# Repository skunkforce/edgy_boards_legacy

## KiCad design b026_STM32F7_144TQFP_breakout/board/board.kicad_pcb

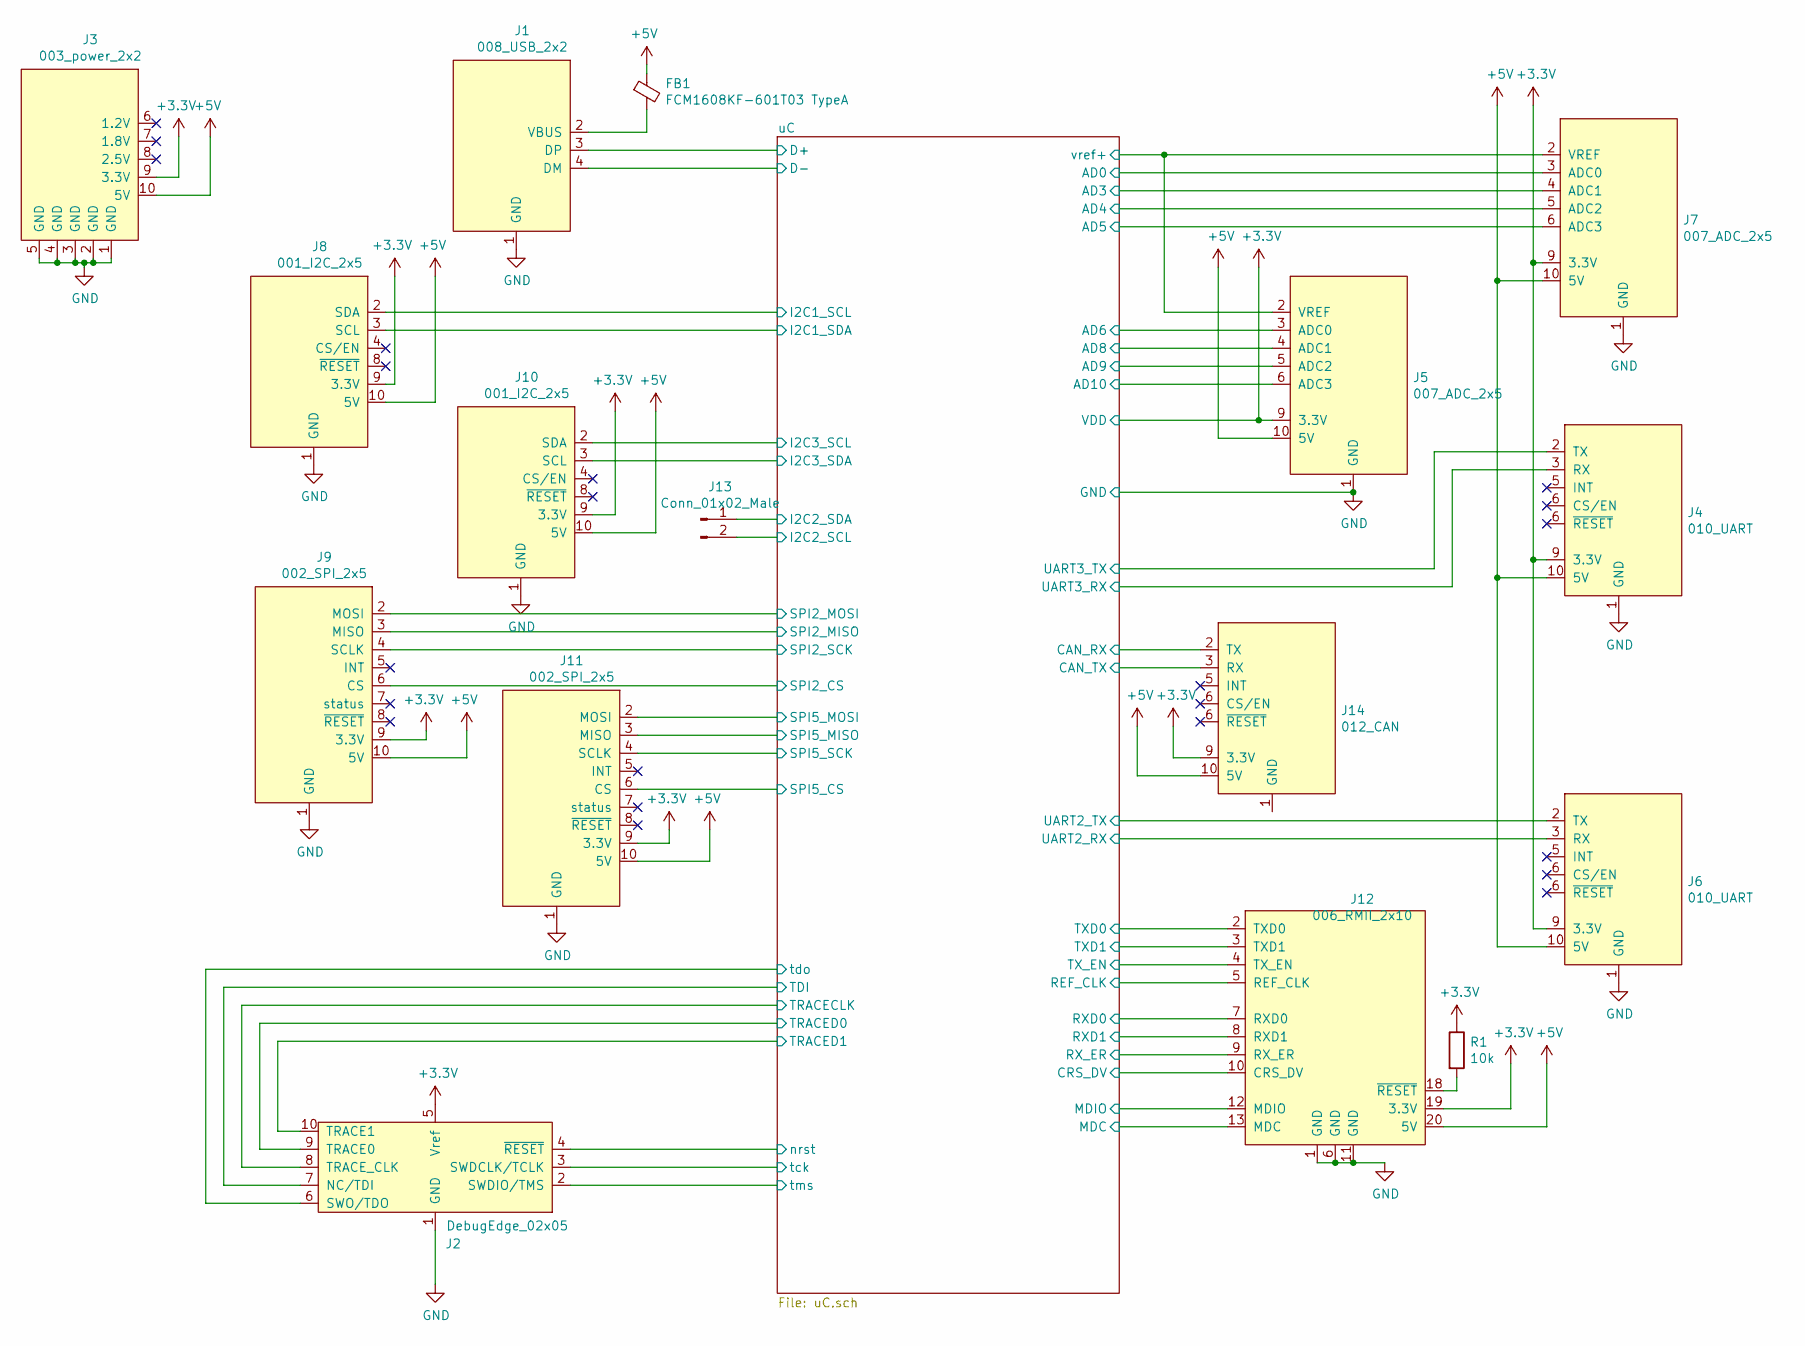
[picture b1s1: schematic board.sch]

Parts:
FB1: FCM1608KF-601T03 TypeA; L_0805_2012Metric
J1: 008_USB_2x2; on_edge_2x05_device
J2: DebugEdge_02x05; on_edge_2x05_device
J3: 003_power_2x2; on_edge_2x05_device
J4: 010_UART; on_edge_2x05_device
J5, J7: 007_ADC_2x5; on_edge_2x05_host
J6: 010_UART; on_edge_2x05_up_host
J8, J10: 001_I2C_2x5; on_edge_2x05_up_host
J9, J11: 002_SPI_2x5; on_edge_2x05_up_host
J12: 006_RMII_2x10; on_edge_2x10_host
J13: Conn_01x02_Male; PinHeader_1x02_P2.00mm_Vertical
J14: 012_CAN; on_edge_2x05_up_host
R1: 10k; R_0603_1608Metric_Pad1.05x0.95mm_HandSolder

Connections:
+3V3: J2.5 (Vref), J3.9 (3.3V), J4.9 (3.3V), J5.9 (3.3V), J6.9 (3.3V), J7.9 (3.3V), J8.9 (3.3V), J9.9 (3.3V), J10.9 (3.3V), J11.9 (3.3V), J12.19 (3.3V), J14.9 (3.3V), R1.1; also elsewhere on the board
+5V: FB1.1, J3.10 (5V), J4.10 (5V), J5.10 (5V), J6.10 (5V), J7.10 (5V), J8.10 (5V), J9.10 (5V), J10.10 (5V), J11.10 (5V), J12.20 (5V), J14.10 (5V)
/uC/AD0: J7.3 (ADC0); also elsewhere on the board
/uC/AD3: J7.4 (ADC1); also elsewhere on the board
/uC/AD4: J7.5 (ADC2); also elsewhere on the board
/uC/AD5: J7.6 (ADC3); also elsewhere on the board
/uC/AD6: J5.3 (ADC0); also elsewhere on the board
/uC/AD8: J5.4 (ADC1); also elsewhere on the board
/uC/AD9: J5.5 (ADC2); also elsewhere on the board
/uC/AD10: J5.6 (ADC3); also elsewhere on the board
/uC/CAN_RX: J14.2 (TX); also elsewhere on the board
/uC/CAN_TX: J14.3 (RX); also elsewhere on the board
/uC/CRS_DV: J12.10 (CRS_DV); also elsewhere on the board
/uC/D+: J1.3 (DP); also elsewhere on the board
/uC/D-: J1.4 (DM); also elsewhere on the board
/uC/I2C1_SCL: J8.2 (SDA); also elsewhere on the board
/uC/I2C1_SDA: J8.3 (SCL); also elsewhere on the board
/uC/I2C2_SCL: J13.2; also elsewhere on the board
/uC/I2C2_SDA: J13.1; also elsewhere on the board
/uC/I2C3_SCL: J10.2 (SDA); also elsewhere on the board
/uC/I2C3_SDA: J10.3 (SCL); also elsewhere on the board
/uC/MDC: J12.13 (MDC); also elsewhere on the board
/uC/MDIO: J12.12 (MDIO); also elsewhere on the board
/uC/REF_CLK: J12.5 (REF_CLK); also elsewhere on the board
/uC/RXD0: J12.7 (RXD0); also elsewhere on the board
/uC/RXD1: J12.8 (RXD1); also elsewhere on the board
/uC/RX_ER: J12.9 (RX_ER); also elsewhere on the board
/uC/SPI2_CS: J9.6 (CS); also elsewhere on the board
/uC/SPI2_MISO: J9.3 (MISO); also elsewhere on the board
/uC/SPI2_MOSI: J9.2 (MOSI); also elsewhere on the board
/uC/SPI2_SCK: J9.4 (SCLK); also elsewhere on the board
/uC/SPI5_CS: J11.6 (CS); also elsewhere on the board
/uC/SPI5_MISO: J11.3 (MISO); also elsewhere on the board
/uC/SPI5_MOSI: J11.2 (MOSI); also elsewhere on the board
/uC/SPI5_SCK: J11.4 (SCLK); also elsewhere on the board
/uC/TDI: J2.7 (NC/TDI); also elsewhere on the board
/uC/TRACECLK: J2.8 (TRACE_CLK); also elsewhere on the board
/uC/TRACED0: J2.9 (TRACE0); also elsewhere on the board
/uC/TRACED1: J2.10 (TRACE1); also elsewhere on the board
/uC/TXD0: J12.2 (TXD0); also elsewhere on the board
/uC/TXD1: J12.3 (TXD1); also elsewhere on the board
/uC/TX_EN: J12.4 (TX_EN); also elsewhere on the board
/uC/UART2_RX: J6.3 (RX); also elsewhere on the board
/uC/UART2_TX: J6.2 (TX); also elsewhere on the board
/uC/UART3_RX: J4.3 (RX); also elsewhere on the board
/uC/UART3_TX: J4.2 (TX); also elsewhere on the board
/uC/nrst: J2.4 (~RESET~); also elsewhere on the board
/uC/tck: J2.3 (SWDCLK/TCLK); also elsewhere on the board
/uC/tdo: J2.6 (SWO/TDO); also elsewhere on the board
/uC/tms: J2.2 (SWDIO/TMS); also elsewhere on the board
/uC/vref+: J5.2 (VREF), J7.2 (VREF); also elsewhere on the board
GND: J1.1 (GND), J2.1 (GND), J3.1 (GND), J3.2 (GND), J3.3 (GND), J3.4 (GND), J3.5 (GND), J4.1 (GND), J5.1 (GND), J6.1 (GND), J7.1 (GND), J8.1 (GND), J9.1 (GND), J10.1 (GND), J11.1 (GND), J12.1 (GND), J12.6 (GND), J12.11 (GND); also elsewhere on the board
unnamed: FB1.2, J1.2 (VBUS)
unnamed: J12.18 (~RESET), R1.2

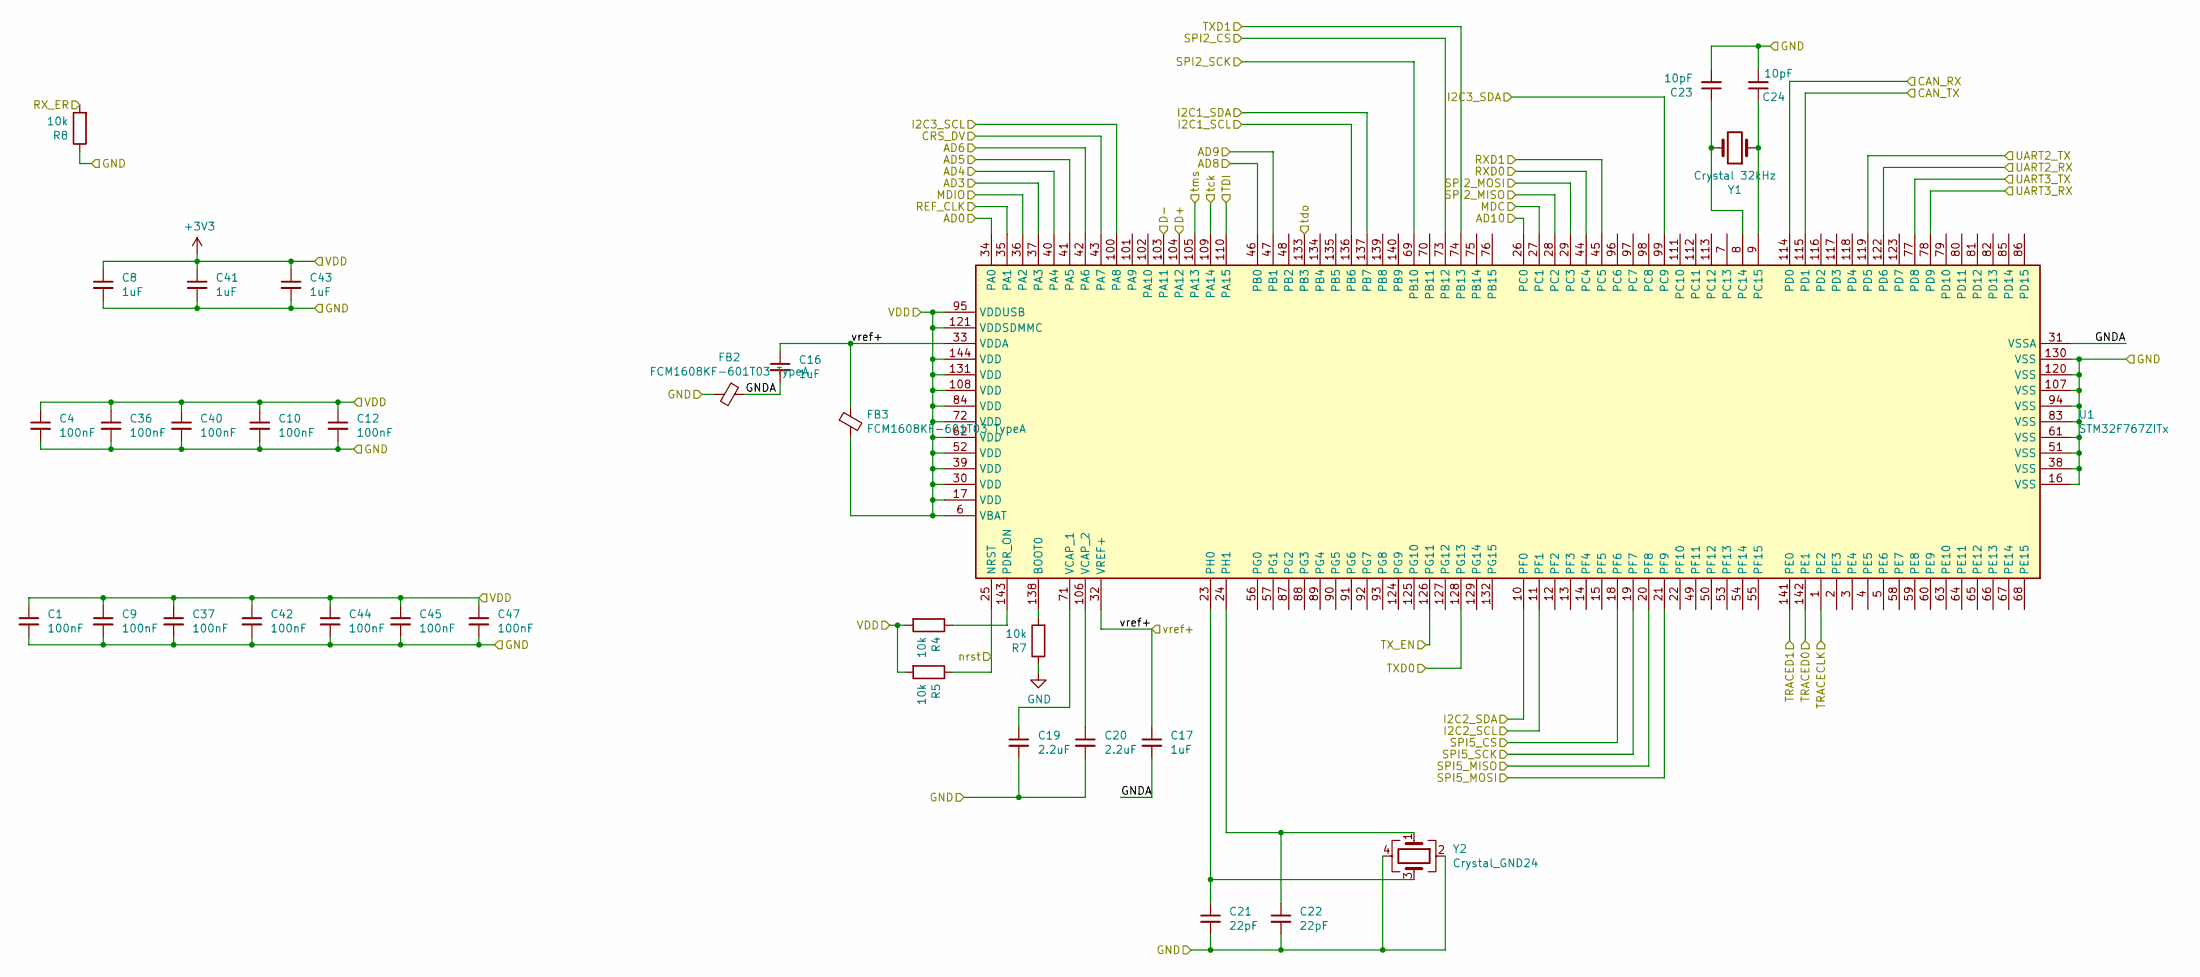
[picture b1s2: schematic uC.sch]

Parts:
C1, C4, C9, C10, C12, C36, C37, C40, C42, C44, C45, C47: 100nF; C_0603_1608Metric
C8, C16, C17, C41, C43: 1uF; C_0603_1608Metric
C19, C20: 2.2uF; C_0603_1608Metric_Pad1.05x0.95mm_HandSolder
C21, C22: 22pF; C_0603_1608Metric_Pad1.05x0.95mm_HandSolder
C23, C24: 10pF; C_0603_1608Metric_Pad1.05x0.95mm_HandSolder
FB2, FB3: FCM1608KF-601T03 TypeA; L_0805_2012Metric
R4, R5, R7, R8: 10k; R_0603_1608Metric_Pad1.05x0.95mm_HandSolder
U1: STM32F767ZITx; LQFP-144_20x20mm_P0.5mm
Y1: Crystal 32kHz; Crystal_SMD_3215-2Pin_3.2x1.5mm; Digi-Key_PN 644-1156-1-ND
Y2: Crystal_GND24; Crystal_SMD_Abracon_ABM8G-4Pin_3.2x2.5mm; Digi-Key_PN 535-9140-1-ND

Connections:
+3V3: C1.1, C4.1, C8.1, C9.1, C10.1, C12.1, C36.1, C37.1, C40.1, C41.1, C42.1, C43.1, C44.1, C45.1, C47.1, FB3.2, R4.2, R5.2, U1.6 (VBAT), U1.17 (VDD), U1.30 (VDD), U1.39 (VDD), U1.52 (VDD), U1.62 (VDD), U1.72 (VDD), U1.84 (VDD), U1.95 (VDDUSB), U1.108 (VDD), U1.121 (VDDSDMMC), U1.131 (VDD), U1.144 (VDD); also elsewhere on the board
/uC/AD0: U1.34 (PA0); also elsewhere on the board
/uC/AD3: U1.37 (PA3); also elsewhere on the board
/uC/AD4: U1.40 (PA4); also elsewhere on the board
/uC/AD5: U1.41 (PA5); also elsewhere on the board
/uC/AD6: U1.42 (PA6); also elsewhere on the board
/uC/AD8: U1.46 (PB0); also elsewhere on the board
/uC/AD9: U1.47 (PB1); also elsewhere on the board
/uC/AD10: U1.26 (PC0); also elsewhere on the board
/uC/CAN_RX: U1.114 (PD0); also elsewhere on the board
/uC/CAN_TX: U1.115 (PD1); also elsewhere on the board
/uC/CRS_DV: U1.43 (PA7); also elsewhere on the board
/uC/D+: U1.104 (PA12); also elsewhere on the board
/uC/D-: U1.103 (PA11); also elsewhere on the board
/uC/GNDA: C16.2, C17.2, FB2.1, U1.31 (VSSA)
/uC/I2C1_SCL: U1.136 (PB6); also elsewhere on the board
/uC/I2C1_SDA: U1.137 (PB7); also elsewhere on the board
/uC/I2C2_SCL: U1.11 (PF1); also elsewhere on the board
/uC/I2C2_SDA: U1.10 (PF0); also elsewhere on the board
/uC/I2C3_SCL: U1.100 (PA8); also elsewhere on the board
/uC/I2C3_SDA: U1.99 (PC9); also elsewhere on the board
/uC/MDC: U1.27 (PC1); also elsewhere on the board
/uC/MDIO: U1.36 (PA2); also elsewhere on the board
/uC/REF_CLK: U1.35 (PA1); also elsewhere on the board
/uC/RXD0: U1.44 (PC4); also elsewhere on the board
/uC/RXD1: U1.45 (PC5); also elsewhere on the board
/uC/RX_ER: R8.2; also elsewhere on the board
/uC/SPI2_CS: U1.73 (PB12); also elsewhere on the board
/uC/SPI2_MISO: U1.28 (PC2); also elsewhere on the board
/uC/SPI2_MOSI: U1.29 (PC3); also elsewhere on the board
/uC/SPI2_SCK: U1.69 (PB10); also elsewhere on the board
/uC/SPI5_CS: U1.18 (PF6); also elsewhere on the board
/uC/SPI5_MISO: U1.20 (PF8); also elsewhere on the board
/uC/SPI5_MOSI: U1.21 (PF9); also elsewhere on the board
/uC/SPI5_SCK: U1.19 (PF7); also elsewhere on the board
/uC/TDI: U1.110 (PA15); also elsewhere on the board
/uC/TRACECLK: U1.1 (PE2); also elsewhere on the board
/uC/TRACED0: U1.142 (PE1); also elsewhere on the board
/uC/TRACED1: U1.141 (PE0); also elsewhere on the board
/uC/TXD0: U1.128 (PG13); also elsewhere on the board
/uC/TXD1: U1.74 (PB13); also elsewhere on the board
/uC/TX_EN: U1.126 (PG11); also elsewhere on the board
/uC/UART2_RX: U1.122 (PD6); also elsewhere on the board
/uC/UART2_TX: U1.119 (PD5); also elsewhere on the board
/uC/UART3_RX: U1.78 (PD9); also elsewhere on the board
/uC/UART3_TX: U1.77 (PD8); also elsewhere on the board
/uC/nrst: R5.1, U1.25 (NRST); also elsewhere on the board
/uC/tck: U1.109 (PA14); also elsewhere on the board
/uC/tdo: U1.133 (PB3); also elsewhere on the board
/uC/tms: U1.105 (PA13); also elsewhere on the board
/uC/vref+: C16.1, C17.1, FB3.1, U1.32 (VREF+), U1.33 (VDDA); also elsewhere on the board
GND: C1.2, C4.2, C8.2, C9.2, C10.2, C12.2, C19.2, C20.2, C21.2, C22.2, C23.2, C24.2, C36.2, C37.2, C40.2, C41.2, C42.2, C43.2, C44.2, C45.2, C47.2, FB2.2, R7.1, R8.1, U1.16 (VSS), U1.38 (VSS), U1.51 (VSS), U1.61 (VSS), U1.83 (VSS), U1.94 (VSS), U1.107 (VSS), U1.120 (VSS), U1.130 (VSS), Y2.2, Y2.4; also elsewhere on the board
unnamed: C19.1, U1.71 (VCAP_1)
unnamed: C20.1, U1.106 (VCAP_2)
unnamed: C21.1, U1.23 (PH0), Y2.3
unnamed: C22.1, U1.24 (PH1), Y2.1
unnamed: C23.1, U1.8 (PC14), Y1.2
unnamed: C24.1, U1.9 (PC15), Y1.1
unnamed: R4.1, U1.143 (PDR_ON)
unnamed: R7.2, U1.138 (BOOT0)

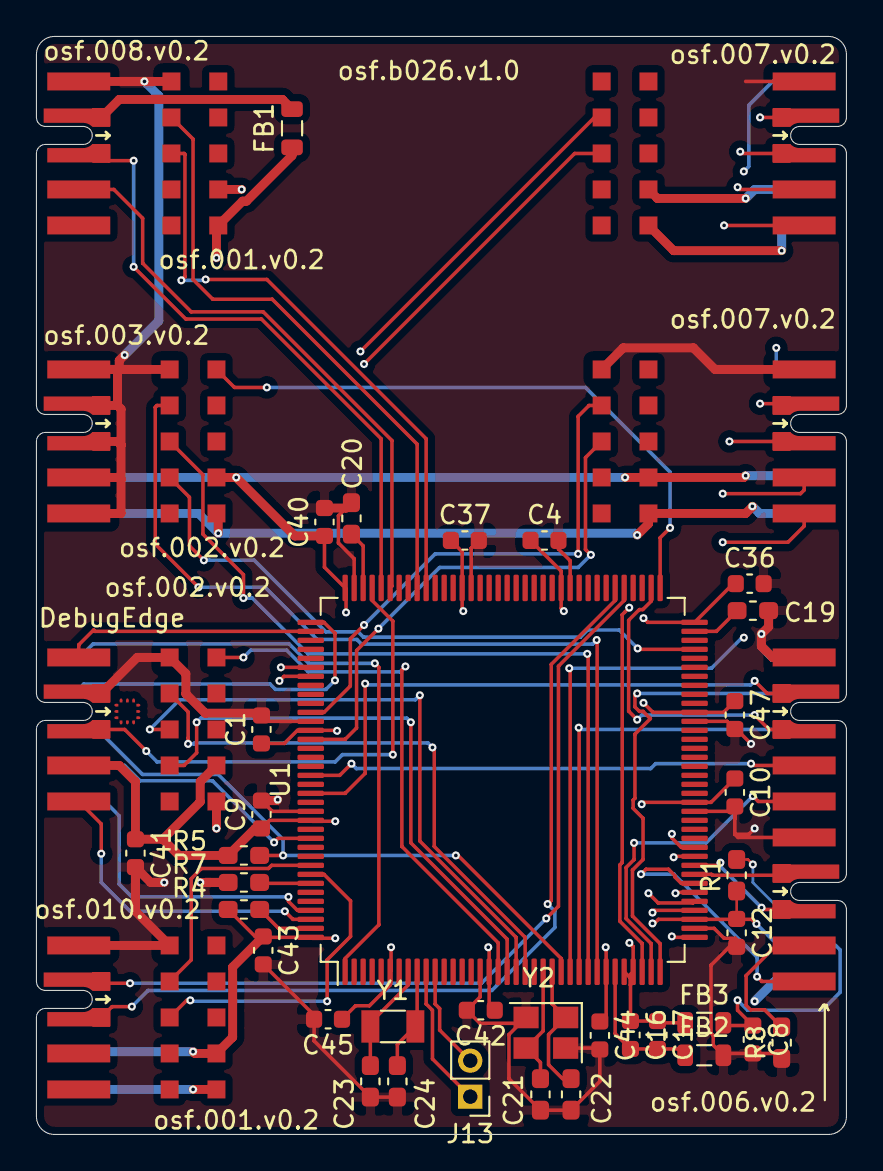
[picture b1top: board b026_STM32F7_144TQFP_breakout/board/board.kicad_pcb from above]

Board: 4 copper layers, 45.0 x 61.0 mm, 48 parts (0 on the bottom side), 63 nets.

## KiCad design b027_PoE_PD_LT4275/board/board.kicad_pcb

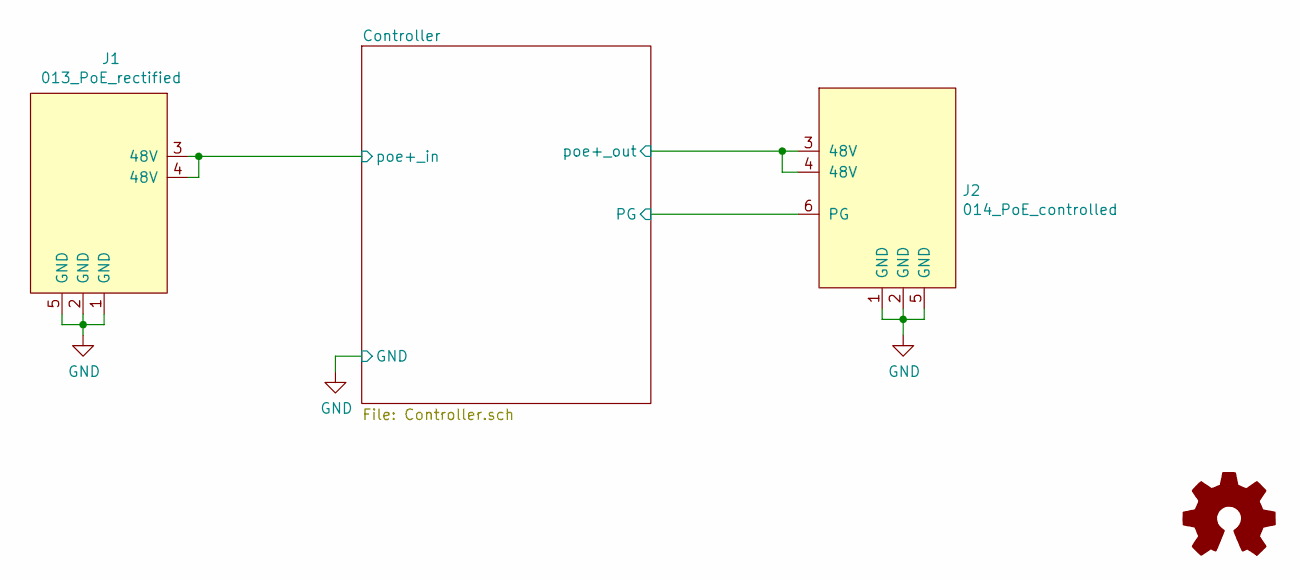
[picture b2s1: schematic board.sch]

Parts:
J1: 013_PoE_rectified; on_edge_2x05_device
J2: 014_PoE_controlled; on_edge_2x05_host
LOGO1: Logo_Open_Hardware_Small; OSHW-Logo2_9.8x8mm_SilkScreen

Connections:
/Controller/PG: J2.6 (PG); also elsewhere on the board
/Controller/poe+_in: J1.3 (48V), J1.4 (48V); also elsewhere on the board
/Controller/poe+_out: J2.3 (48V), J2.4 (48V); also elsewhere on the board
GND: J1.1 (GND), J1.2 (GND), J1.5 (GND), J2.1 (GND), J2.2 (GND), J2.5 (GND); also elsewhere on the board

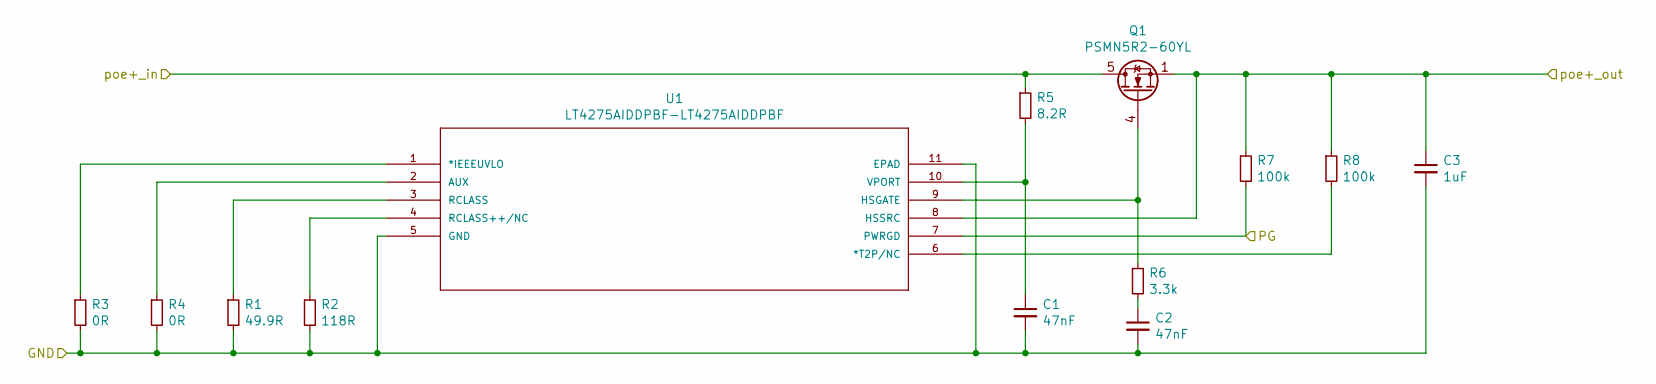
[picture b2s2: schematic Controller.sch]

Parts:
C1, C2: 47nF; C_0603_1608Metric
C3: 1uF; C_1206_3216Metric; Voltage 100
Q1: PSMN5R2-60YL; LFPAK33
R1: 49.9R; R_0603_1608Metric
R2: 118R; R_0603_1608Metric
R3, R4: 0R; R_0603_1608Metric
R5: 8.2R; R_0603_1608Metric
R6: 3.3k; R_0603_1608Metric
R7, R8: 100k; R_0603_1608Metric
U1: LT4275AIDDPBF-LT4275AIDDPBF; DFN-10-1EP_3x3mm_P0.5mm_EP1.65x2.38mm; MANUFACTURER_PART_NUMBER lt4275aidd#pbf

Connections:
/Controller/PG: R7.2, U1.7 (PWRGD); also elsewhere on the board
/Controller/poe+_in: Q1.5 (D), R5.1; also elsewhere on the board
/Controller/poe+_out: C3.1, Q1.1 (S), Q1.2 (S), Q1.3 (S), R7.1, R8.1, U1.8 (HSSRC); also elsewhere on the board
GND: C1.2, C2.2, C3.2, R1.2, R2.2, R3.2, R4.2, U1.5 (GND), U1.11 (EPAD); also elsewhere on the board
unnamed: C1.1, R5.2, U1.10 (VPORT)
unnamed: C2.1, R6.2
unnamed: Q1.4 (G), R6.1, U1.9 (HSGATE)
unnamed: R1.1, U1.3 (RCLASS)
unnamed: R2.1, U1.4 (RCLASS++/NC)
unnamed: R3.1, U1.1 (*IEEEUVLO)
unnamed: R4.1, U1.2 (AUX)
unnamed: R8.2, U1.6 (*T2P/NC)

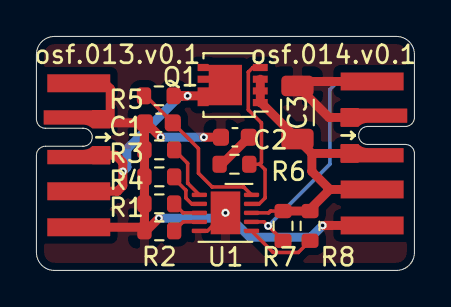
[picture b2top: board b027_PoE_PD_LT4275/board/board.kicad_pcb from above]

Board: 2 copper layers, 21.0 x 13.0 mm, 16 parts (1 on the bottom side), 12 nets.

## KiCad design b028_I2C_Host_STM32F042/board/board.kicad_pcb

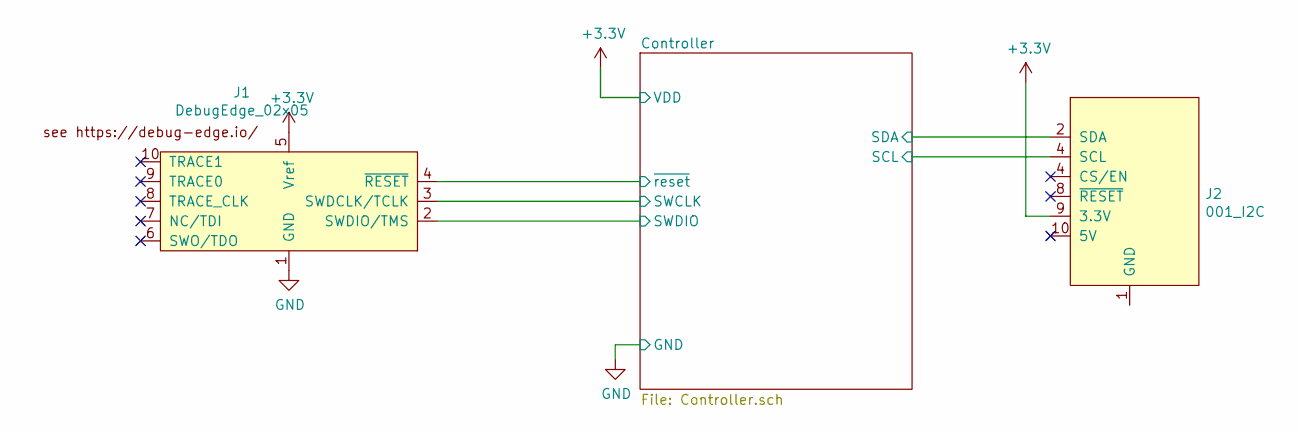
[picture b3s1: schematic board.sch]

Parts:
J1: DebugEdge_02x05; on_edge_2x05_device
J2: 001_I2C; on_edge_2x05_host

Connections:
+3V3: J1.5 (Vref), J2.9 (3.3V); also elsewhere on the board
/Controller/SCL: J2.4 (CS/EN); also elsewhere on the board
/Controller/SDA: J2.2 (SDA); also elsewhere on the board
/Controller/SWCLK: J1.3 (SWDCLK/TCLK); also elsewhere on the board
/Controller/SWDIO: J1.2 (SWDIO/TMS); also elsewhere on the board
/Controller/~reset: J1.4 (~RESET~); also elsewhere on the board
GND: J1.1 (GND); also elsewhere on the board

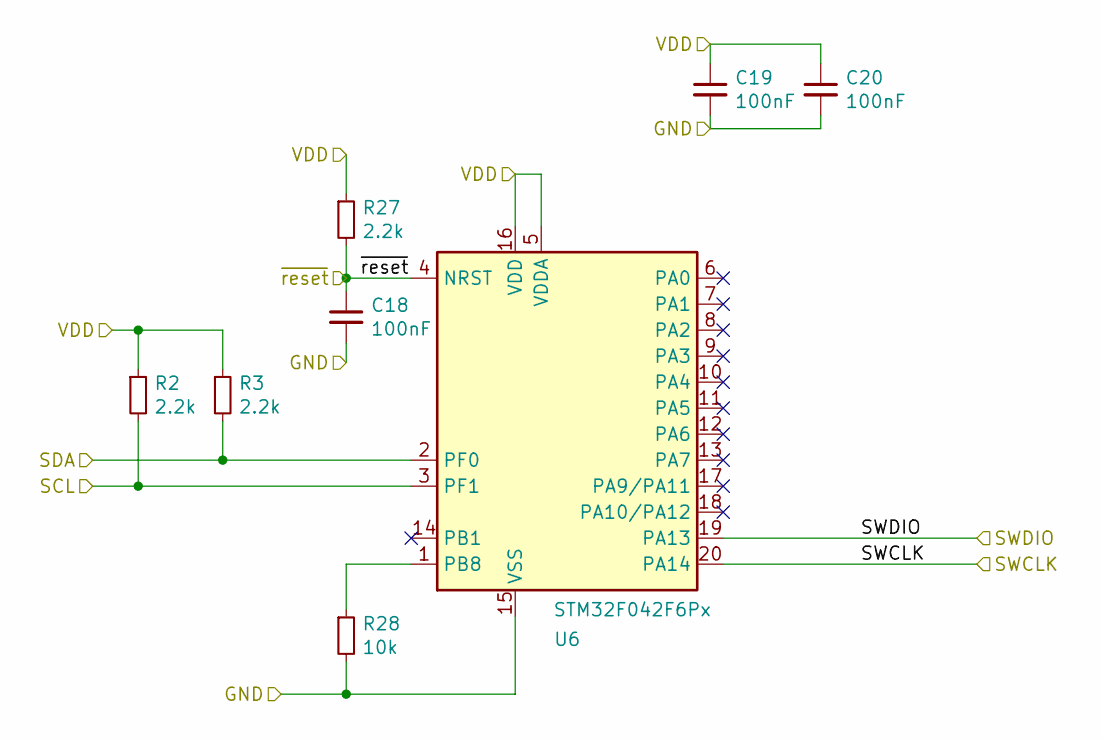
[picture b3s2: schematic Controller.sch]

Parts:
C18, C19, C20: 100nF; C_0603_1608Metric
R2, R3, R27: 2.2k; R_0603_1608Metric
R28: 10k; R_0603_1608Metric
U6: STM32F042F6Px; TSSOP-20_4.4x6.5mm_P0.65mm; MPN STM32F042F4P6; Digi-Key_PN 497-17343-ND

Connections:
+3V3: C19.1, C20.1, R2.1, R3.1, R27.1, U6.5 (VDDA), U6.16 (VDD); also elsewhere on the board
/Controller/SCL: R2.2, U6.3 (PF1); also elsewhere on the board
/Controller/SDA: R3.2, U6.2 (PF0); also elsewhere on the board
/Controller/SWCLK: U6.20 (PA14); also elsewhere on the board
/Controller/SWDIO: U6.19 (PA13); also elsewhere on the board
/Controller/~reset: C18.1, R27.2, U6.4 (NRST); also elsewhere on the board
GND: C18.2, C19.2, C20.2, R28.2, U6.15 (VSS); also elsewhere on the board
unnamed: R28.1, U6.1 (PB8)

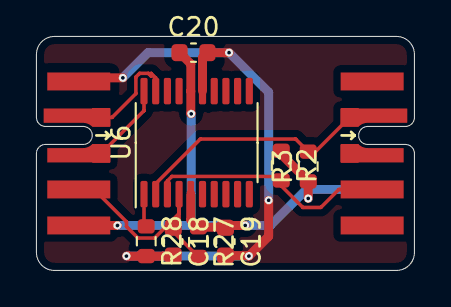
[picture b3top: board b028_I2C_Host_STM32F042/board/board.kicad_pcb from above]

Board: 2 copper layers, 21.0 x 13.0 mm, 10 parts (0 on the bottom side), 8 nets.

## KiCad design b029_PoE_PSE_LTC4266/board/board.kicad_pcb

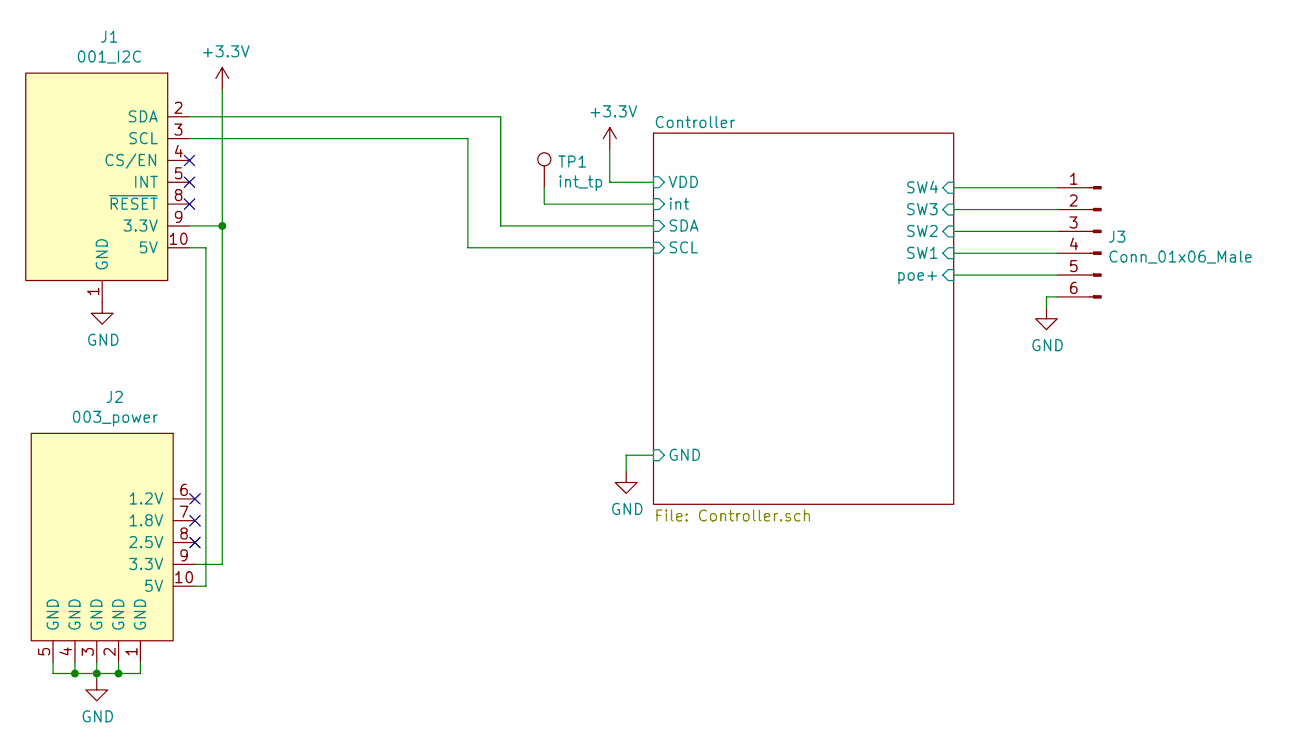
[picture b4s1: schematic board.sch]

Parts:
J1: 001_I2C; on_edge_2x05_device
J2: 003_power; on_edge_2x05_device
J3: Conn_01x06_Male; PinHeader_1x06_P2.54mm_Vertical
TP1: int_tp; TestPoint_Pad_2.0x2.0mm

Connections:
+3V3: J1.9 (3.3V), J2.9 (3.3V); also elsewhere on the board
/Controller/SCL: J1.3 (SCL); also elsewhere on the board
/Controller/SDA: J1.2 (SDA); also elsewhere on the board
/Controller/SW1: J3.4; also elsewhere on the board
/Controller/SW2: J3.3; also elsewhere on the board
/Controller/SW3: J3.2; also elsewhere on the board
/Controller/SW4: J3.1; also elsewhere on the board
/Controller/int: TP1.1; also elsewhere on the board
/Controller/poe+: J3.5; also elsewhere on the board
GND: J1.1 (GND), J2.1 (GND), J2.2 (GND), J2.3 (GND), J2.4 (GND), J2.5 (GND), J3.6; also elsewhere on the board
unnamed: J1.10 (5V), J2.10 (5V)

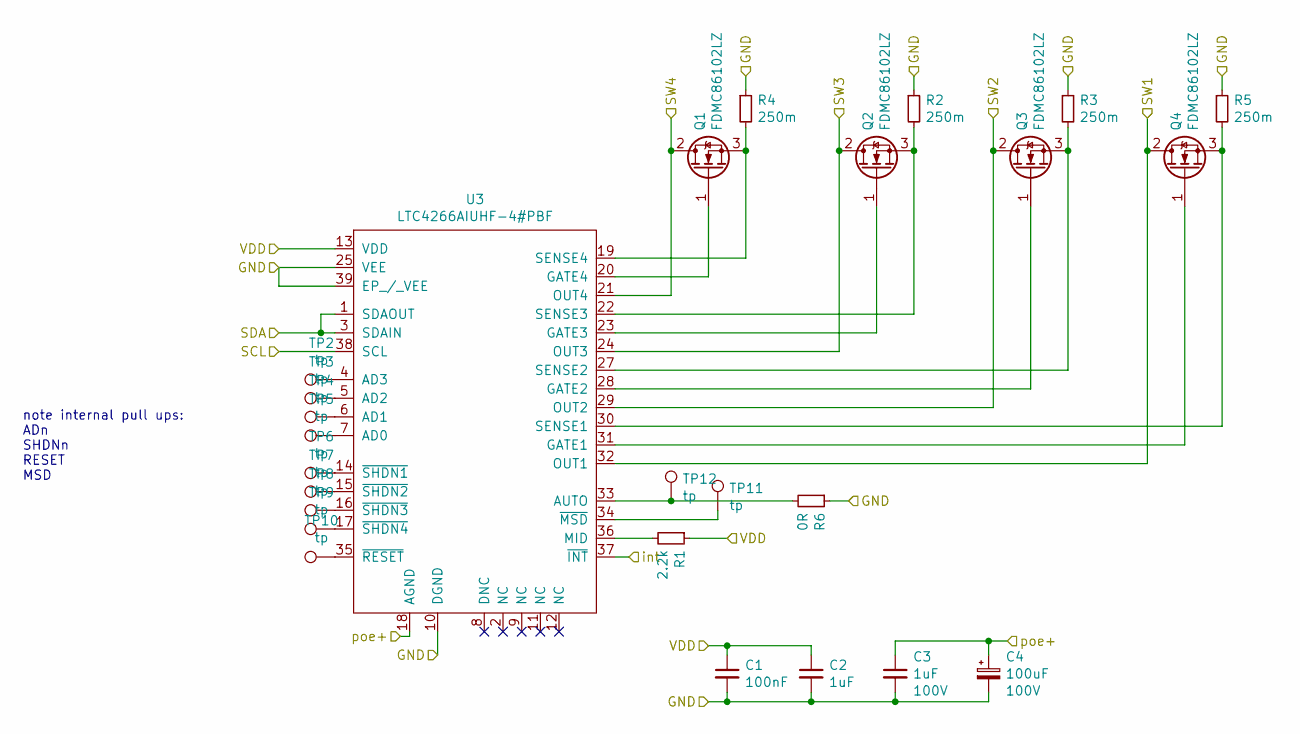
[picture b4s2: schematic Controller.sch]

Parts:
C1: 100nF; C_0805_2012Metric
C2: 1uF; C_0805_2012Metric
C3: 1uF; C_0805_2012Metric; voltage 100V
C4: 100uF; CP_Elec_8x5.4; voltage 100V
Q1, Q2, Q3, Q4: FDMC86102LZ; TRANS_FDMC86102LZ; MPN FDMC86102LZ; Digi-Key_PN FDMC86102LZCT-ND
R1: 2.2k; R_0402_1005Metric
R2, R3, R4, R5: 250m; R_2512_6332Metric; MPN CSRN2512FKR250
R6: 0R; R_0402_1005Metric
TP2, TP3, TP4, TP5, TP6, TP7, TP8, TP9, TP10, TP11, TP12: tp; TestPoint_Pad_2.0x2.0mm
U3: LTC4266AIUHF-4#PBF; QFN-38-1EP_5x7mm_P0.5mm_EP3.15x5.15mm; MPN LTC4266AIUHF-4#PBF; Digi-Key_PN LTC4266AIUHF-4#PBF-ND

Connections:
+3V3: C1.1, C2.1, R1.1, U3.13 (VDD); also elsewhere on the board
/Controller/SCL: U3.38 (SCL); also elsewhere on the board
/Controller/SDA: U3.1 (SDAOUT), U3.3 (SDAIN); also elsewhere on the board
/Controller/SW1: Q4.2 (D), U3.32 (OUT1); also elsewhere on the board
/Controller/SW2: Q3.2 (D), U3.29 (OUT2); also elsewhere on the board
/Controller/SW3: Q2.2 (D), U3.24 (OUT3); also elsewhere on the board
/Controller/SW4: Q1.2 (D), U3.21 (OUT4); also elsewhere on the board
/Controller/int: U3.37 (~INT); also elsewhere on the board
/Controller/poe+: C3.1, C4.1, U3.18 (AGND); also elsewhere on the board
GND: C1.2, C2.2, C3.2, C4.2, R2.1, R3.1, R4.1, R5.1, R6.1, U3.10 (DGND), U3.25 (VEE), U3.26 (VEE), U3.39 (EP_/_VEE); also elsewhere on the board
unnamed: Q1.1 (G), U3.20 (GATE4)
unnamed: Q1.3 (S), R4.2, U3.19 (SENSE4)
unnamed: Q2.1 (G), U3.23 (GATE3)
unnamed: Q2.3 (S), R2.2, U3.22 (SENSE3)
unnamed: Q3.1 (G), U3.28 (GATE2)
unnamed: Q3.3 (S), R3.2, U3.27 (SENSE2)
unnamed: Q4.1 (G), U3.31 (GATE1)
unnamed: Q4.3 (S), R5.2, U3.30 (SENSE1)
unnamed: R1.2, U3.36 (MID)
unnamed: R6.2, TP12.1, U3.33 (AUTO)
unnamed: TP2.1, U3.4 (AD3)
unnamed: TP3.1, U3.5 (AD2)
unnamed: TP4.1, U3.6 (AD1)
unnamed: TP5.1, U3.7 (AD0)
unnamed: TP6.1, U3.14 (~SHDN1)
unnamed: TP7.1, U3.15 (~SHDN2)
unnamed: TP8.1, U3.16 (~SHDN3)
unnamed: TP9.1, U3.17 (~SHDN4)
unnamed: TP10.1, U3.35 (~RESET)
unnamed: TP11.1, U3.34 (~MSD)

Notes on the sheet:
note internal pull ups: ADn SHDNn RESET MSD

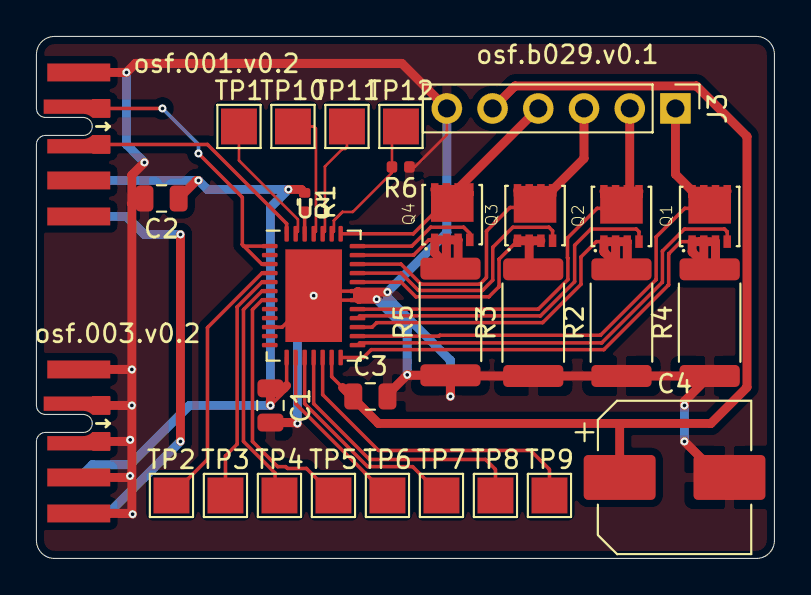
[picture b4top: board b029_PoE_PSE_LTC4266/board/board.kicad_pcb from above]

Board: 2 copper layers, 41.0 x 29.0 mm, 30 parts (0 on the bottom side), 31 nets.

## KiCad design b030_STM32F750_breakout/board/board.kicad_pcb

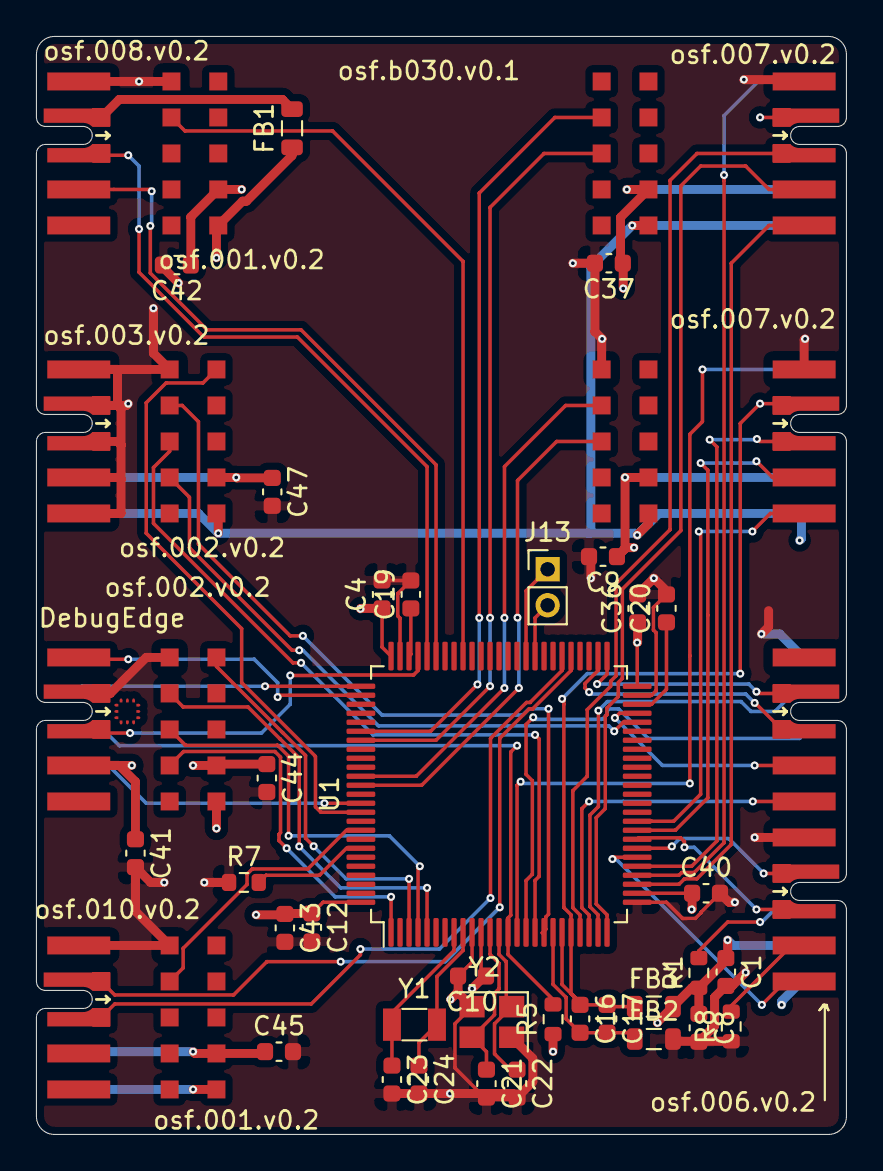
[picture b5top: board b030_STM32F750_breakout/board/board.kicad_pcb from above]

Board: 4 copper layers, 45.0 x 61.0 mm, 47 parts (0 on the bottom side), 57 nets.

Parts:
C1, C4, C9, C10, C12, C36, C37, C40, C42, C44, C45, C47: 100nF; C_0603_1608Metric
C8, C16, C17, C41, C43: 1uF; C_0603_1608Metric
C19, C20: 2.2uF; C_0603_1608Metric
C21, C22: 22pF; C_0603_1608Metric
C23, C24: 10pF; C_0603_1608Metric
FB1: Ferrite_Bead_Small; L_0805_2012Metric
FB2, FB3: FCM1608KF-601T03 TypeA; L_0805_2012Metric
J1: 008_USB_2x2; on_edge_2x05_device
J2: DebugEdge_02x05; on_edge_2x05_device
J3: 003_power_2x2; on_edge_2x05_device
J4: 010_UART; on_edge_2x05_device
J5, J7: 007_ADC_2x5; on_edge_2x05_host
J6: 010_UART; on_edge_2x05_up_host
J8, J10: 001_I2C_2x5; on_edge_2x05_up_host
J9, J11: 002_SPI_2x5; on_edge_2x05_up_host
J12: 006_RMII_2x10; on_edge_2x10_host
J13: Conn_01x02_Male; PinHeader_1x02_P2.00mm_Vertical
J14: 012_CAN; on_edge_2x05_up_host
R1, R5, R7, R8: 10k; R_0603_1608Metric
U1: STM32F750V8T6-STM32F750V8T6; LQFP-100_14x14mm_P0.5mm
Y1: Crystal 32kHz; Crystal_SMD_3215-2Pin_3.2x1.5mm
Y2: Crystal_GND24; Crystal_SMD_Abracon_ABM8G-4Pin_3.2x2.5mm

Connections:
+3V3: C1.1, C4.1, C8.1, C9.1, C10.1, C12.1, C36.1, C37.1, C40.1, C41.1, C42.1, C43.1, C44.1, C45.1, C47.1, FB3.2, J2.5, J3.9, J4.9, J5.9, J6.9, J7.9, J8.9, J9.9, J10.9, J11.9, J12.19, J14.9, R1.1, R5.1, U1.11, U1.27, U1.50, U1.75, U1.100
+5V: FB1.1, J3.10, J4.10, J5.10, J6.10, J7.10, J8.10, J9.10, J10.10, J11.10, J12.20, J14.10
/uC/AD0: J7.3, U1.22
/uC/AD3: J7.4, U1.25
/uC/AD4: J7.5, U1.28
/uC/AD5: J7.6, U1.29
/uC/AD6: J5.3, U1.30
/uC/AD8: J5.4, U1.34
/uC/AD9: J5.5, U1.35
/uC/AD10: J5.6, U1.15
/uC/CAN_RX: J14.2, U1.81
/uC/CAN_TX: J14.3, U1.82
/uC/CRS_DV: J12.10, U1.31
/uC/D+: J1.3, U1.71
/uC/D-: J1.4, U1.70
/uC/GNDA: C16.2, C17.2, FB2.1, U1.19
/uC/I2C1_SCL: J8.2, U1.92
/uC/I2C3_SCL: J10.2, U1.67
/uC/I2C4_SCL: J13.2, U1.59
/uC/I2C4_SDA: J13.1, U1.60
/uC/MDC: J12.13, U1.16
/uC/MDIO: J12.12, U1.24
/uC/REF_CLK: J12.5, U1.23
/uC/RXD0: J12.7, U1.32
/uC/RXD1: J12.8, U1.33
/uC/RX_ER: J12.9, R8.2
/uC/SPI2_CS: J9.6, U1.90
/uC/SPI2_MISO: J9.3, U1.17
/uC/SPI2_MOSI: J9.2, U1.18
/uC/SPI2_SCK: J9.4, U1.46
/uC/SPI4_CS: J11.6, U1.3
/uC/SPI4_MISO: J11.3, U1.4
/uC/SPI4_MOSI: J11.2, U1.5
/uC/SPI4_SCK: J11.4, U1.1
/uC/TDI: J2.7, U1.77
/uC/TXD0: J12.2, U1.51
/uC/TXD1: J12.3, U1.52
/uC/TX_EN: J12.4, U1.47
/uC/UART2_RX: J6.3, U1.87
/uC/UART2_TX: J6.2, U1.86
/uC/UART3_RX: J4.3, U1.56
/uC/UART3_TX: J4.2, U1.55
/uC/nrst: J2.4, R5.2, U1.14
/uC/tck: J2.3, U1.76
/uC/tdo: J2.6, U1.89
/uC/tms: J2.2, U1.72
/uC/vref+: C16.1, C17.1, FB3.1, J5.2, J7.2, U1.20, U1.21
GND: C1.2, C4.2, C8.2, C9.2, C10.2, C12.2, C19.2, C20.2, C21.2, C22.2, C23.2, C24.2, C36.2, C37.2, C40.2, C41.2, C42.2, C43.2, C44.2, C45.2, C47.2, FB2.2, J1.1, J2.1, J3.1, J3.2, J3.3, J3.4, J3.5, J4.1, J5.1, J6.1, J7.1, J8.1, J9.1, J10.1, J11.1, J12.1, J12.6, J12.11, R7.1, R8.1, U1.10, U1.26, U1.49, U1.74, U1.99, Y2.2, Y2.4
unnamed: C19.1, U1.73
unnamed: C20.1, U1.48
unnamed: C21.1, U1.12, Y2.3
unnamed: C22.1, U1.13, Y2.1
unnamed: C23.1, U1.8, Y1.2
unnamed: C24.1, U1.9, Y1.1
unnamed: FB1.2, J1.2
unnamed: J12.18, R1.2
unnamed: R7.2, U1.94
